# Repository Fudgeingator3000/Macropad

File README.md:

# Macropad
This is my own custom macropad i made in kicad.
it was a great learning experience and i had a lot of fun making it.
its very simple and hopefully cheap and has a 3d printable shell.

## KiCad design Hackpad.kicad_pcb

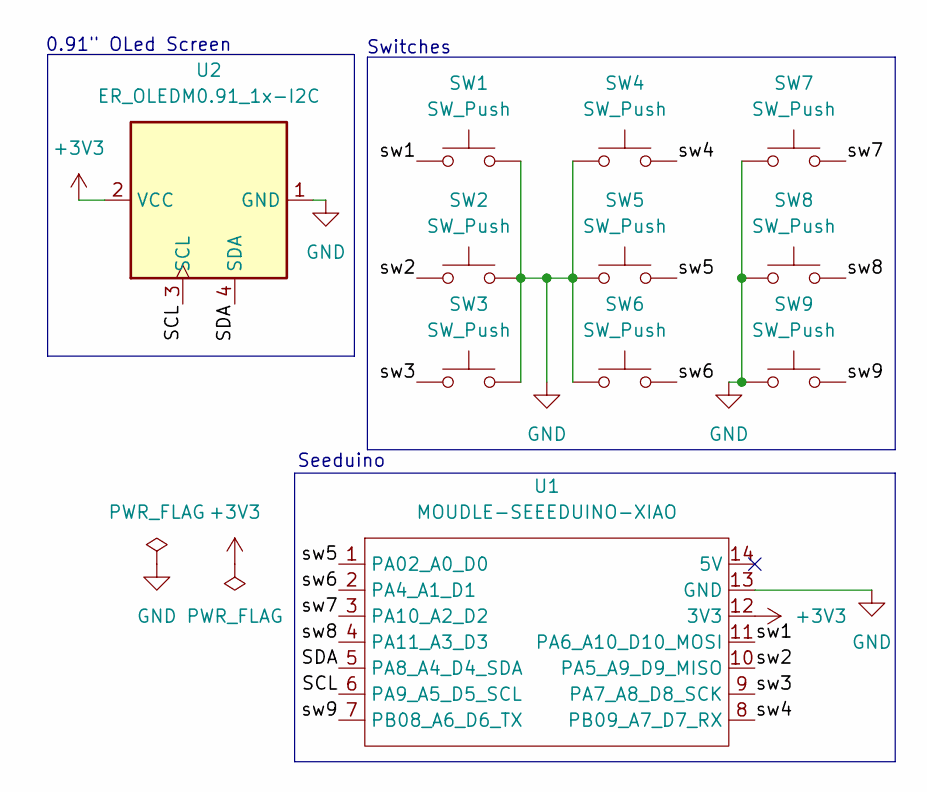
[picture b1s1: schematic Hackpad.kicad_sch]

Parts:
SW1, SW2, SW3, SW4, SW5, SW6, SW7, SW8, SW9: SW_Push; SW_Cherry_MX_1.00u_Plate
U1: MOUDLE-SEEEDUINO-XIAO; XIAO-Generic-Hybrid-14P-2.54-21X17.8MM
U2: ER_OLEDM0.91_1x-I2C

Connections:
+3V3: U1.12 (3V3), U2.2 (VCC)
/SCL: U1.6 (PA9_A5_D5_SCL), U2.3 (SCL)
/SDA: U1.5 (PA8_A4_D4_SDA), U2.4 (SDA)
/sw1: SW1.1, U1.11 (PA6_A10_D10_MOSI)
/sw2: SW2.1, U1.10 (PA5_A9_D9_MISO)
/sw3: SW3.1, U1.9 (PA7_A8_D8_SCK)
/sw4: SW4.2, U1.8 (PB09_A7_D7_RX)
/sw5: SW5.2, U1.1 (PA02_A0_D0)
/sw6: SW6.2, U1.2 (PA4_A1_D1)
/sw7: SW7.2, U1.3 (PA10_A2_D2)
/sw8: SW8.2, U1.4 (PA11_A3_D3)
/sw9: SW9.2, U1.7 (PB08_A6_D6_TX)
GND: SW1.2, SW2.2, SW3.2, SW4.1, SW5.1, SW6.1, SW7.1, SW8.1, SW9.1, U1.13 (GND), U2.1 (GND)

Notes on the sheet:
0.91" OLed Screen
Switches
Seeduino

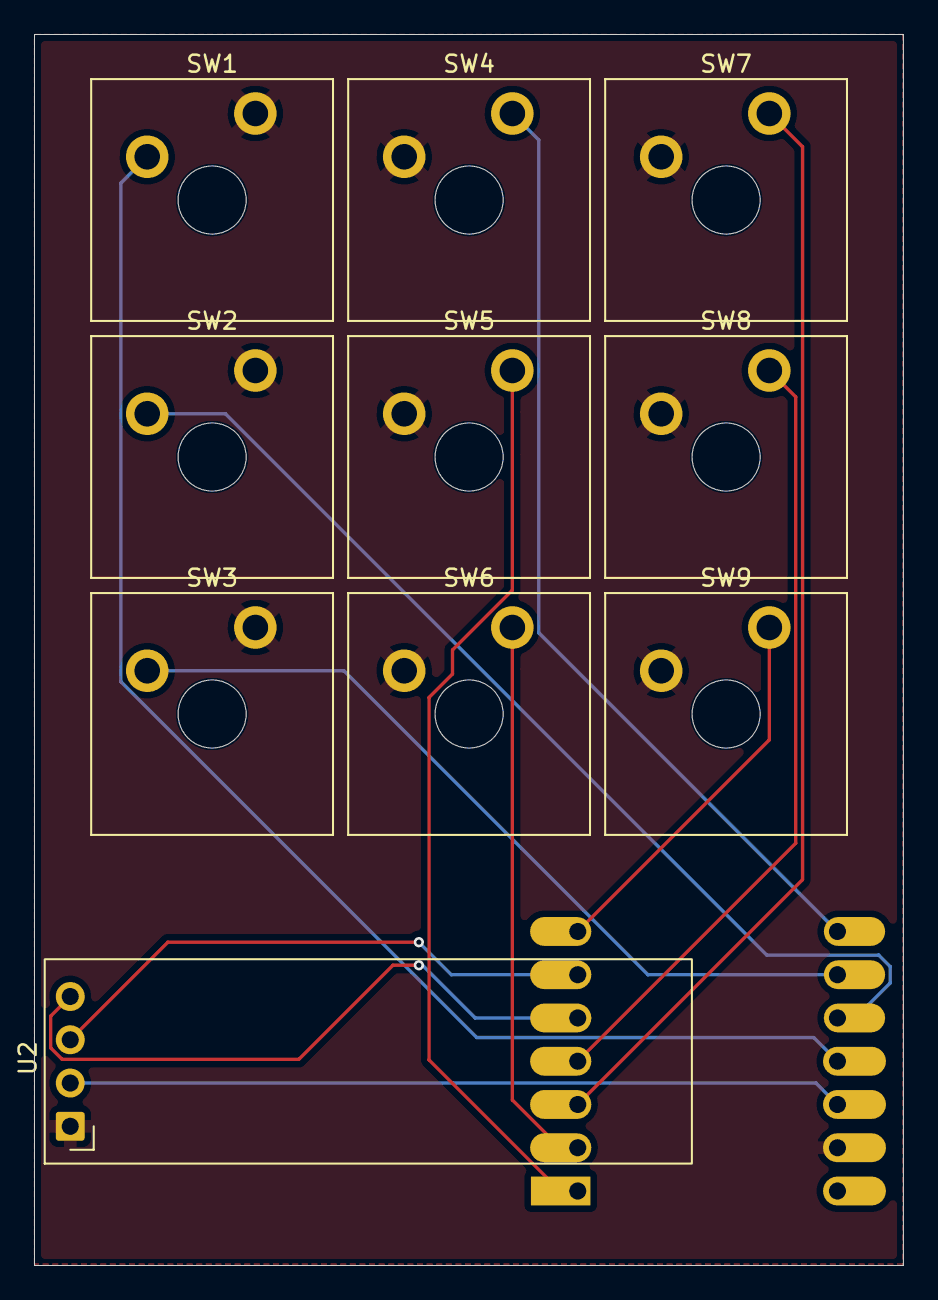
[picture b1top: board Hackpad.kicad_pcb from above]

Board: 2 copper layers, 51.0 x 72.3 mm, 11 parts (1 on the bottom side), 13 nets.
